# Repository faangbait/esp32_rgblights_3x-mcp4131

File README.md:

# esp32_rgblights_3x-mcp4131
Controlling RGB lights strands by sending independent voltages down each wire

This is a WIP, and I fix stuff slow. Read the Issues tab!

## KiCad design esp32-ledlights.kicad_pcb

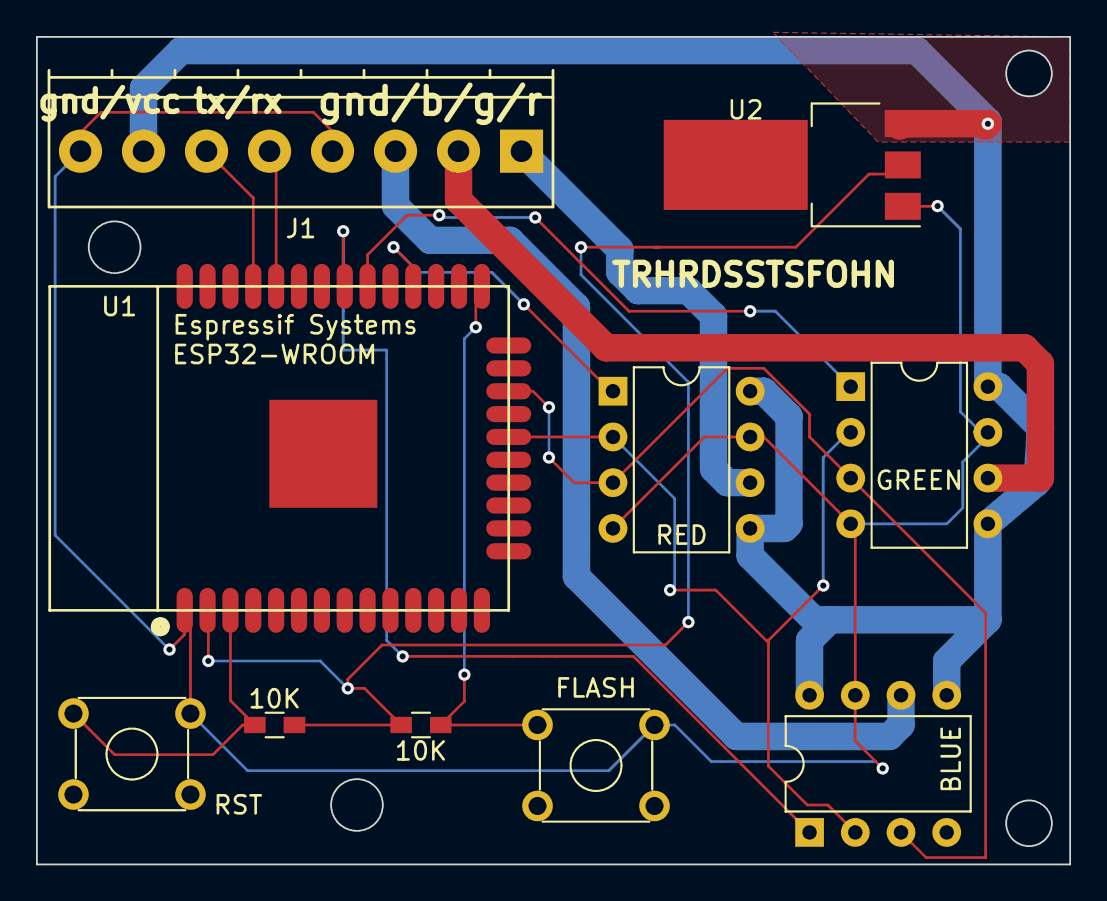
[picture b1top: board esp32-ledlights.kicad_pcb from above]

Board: 2 copper layers, 57.4 x 46.0 mm, 10 parts (0 on the bottom side), 15 nets.

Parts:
10K, 10K#2: R10K; R_0603_HandSoldering
BLUE: MCP4131; DIP-8_W7.62mm
FLASH: SW_Push; SW_TH_Tactile_Omron_B3F-10xx
GREEN: MCP4131; DIP-8_W7.62mm
J1: Screw_Terminal_01x08; TerminalBlock_Phoenix_PT-3.5mm_8pol
RED: MCP4131; DIP-8_W7.62mm
RST: SW_Push; SW_TH_Tactile_Omron_B3F-10xx
U1: ESP32-WROOM
U2: AZ1117-3.3; SOT-223

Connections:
+3V3: 10K.2, 10K#2.2, U1.2, U2.2
+5V: BLUE.5, BLUE.8, GREEN.5, GREEN.8, J1.7, RED.5, RED.8, U2.3
BLUE: BLUE.6, J1.3
CLK: BLUE.2, GREEN.2, RED.2, U1.20
CS1: RED.1, U1.28
CS2: GREEN.1, U1.30
CS3: BLUE.1, U1.31
GND: BLUE.4, BLUE.7, FLASH.2, GREEN.4, GREEN.7, J1.4, J1.8, RED.4, RED.7, RST.2, U1.1, U2.1
GREEN: GREEN.6, J1.2
MOSI: BLUE.3, GREEN.3, RED.3, U1.22
unnamed: 10K#2.1, RST.1, U1.3
unnamed: 10K.1, FLASH.1, U1.25
RED: J1.1, RED.6
RX: J1.5, U1.34
TX: J1.6, U1.35

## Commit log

2018-05-16 Rev 1
2018-05-16 Rev 1 Bugfix
2018-05-16 the lube that holds it all together
2018-05-19 Call this script to show a beautiful sunrise!
2018-06-02 ESP-IDF Source Code with MQTT / Hass.io
2018-06-02 MQTT version
